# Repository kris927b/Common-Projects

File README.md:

# Common-Projects
Projects for AVR-C Microcontroller class KEA

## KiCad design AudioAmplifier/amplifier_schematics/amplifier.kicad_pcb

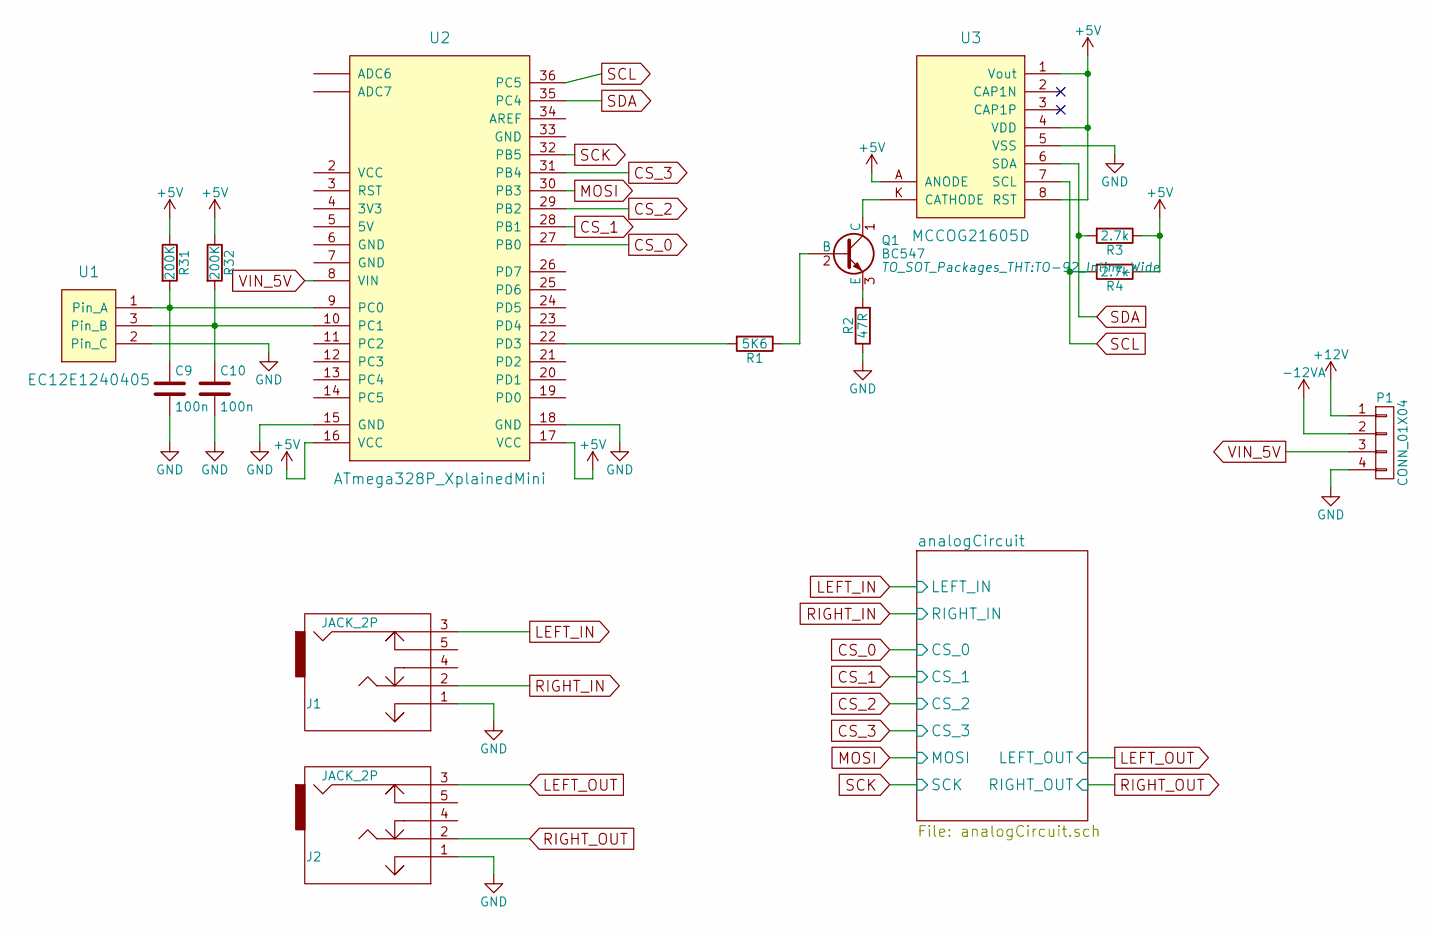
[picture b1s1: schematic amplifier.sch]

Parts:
C9, C10: 100n; C_Disc_D3.0mm_W1.6mm_P2.50mm
J1, J2: JACK_2P; JACK_3,5mm_5pin
P1: CONN_01X04; TerminalBlock_Pheonix_MKDS1.5-4pol
Q1: BC547; TO-92_Inline_Wide
R1: 5K6; R_Axial_DIN0207_L6.3mm_D2.5mm_P10.16mm_Horizontal
R2: 47R; R_Axial_DIN0207_L6.3mm_D2.5mm_P10.16mm_Horizontal
R3, R4: 2.7k; R_Axial_DIN0207_L6.3mm_D2.5mm_P10.16mm_Horizontal
R31, R32: 200K; R_Axial_DIN0207_L6.3mm_D2.5mm_P10.16mm_Horizontal
U1: EC12E1240405; Encoder EC12E
U2: ATmega328P_XplainedMini; xplained_board
U3: MCCOG21605D

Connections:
+5V: R3.1, R4.1, R31.1, R32.1, U2.16 (VCC), U2.17 (VCC), U3.1 (Vout), U3.4 (VDD), U3.8 (RST), U3.A (ANODE); also elsewhere on the board
+12V: P1.1; also elsewhere on the board
-12VA: P1.2; also elsewhere on the board
CS_0: U2.27 (PB0); also elsewhere on the board
CS_1: U2.28 (PB1); also elsewhere on the board
CS_2: U2.29 (PB2); also elsewhere on the board
CS_3: U2.31 (PB4); also elsewhere on the board
GND: C9.2, C10.2, J1.1, J2.1, P1.4, R2.1, U1.2 (Pin_C), U2.15 (GND), U2.18 (GND), U3.5 (VSS); also elsewhere on the board
LEFT_IN: J1.3; also elsewhere on the board
LEFT_OUT: J2.3; also elsewhere on the board
MOSI: U2.30 (PB3); also elsewhere on the board
unnamed: C9.1, R31.2, U1.1 (Pin_A), U2.9 (PC0)
unnamed: C10.1, R32.2, U1.3 (Pin_B), U2.10 (PC1)
unnamed: Q1.1 (C), U3.K (CATHODE)
unnamed: Q1.2 (B), R1.1
unnamed: Q1.3 (E), R2.2
unnamed: R1.2, U2.22 (PD3)
RIGHT_IN: J1.2; also elsewhere on the board
RIGHT_OUT: J2.2; also elsewhere on the board
SCK: U2.32 (PB5); also elsewhere on the board
SCL: R4.2, U2.36 (PC5), U3.7 (SCL)
SDA: R3.2, U2.35 (PC4), U3.6 (SDA)
VIN_5V: P1.3, U2.8 (VIN)

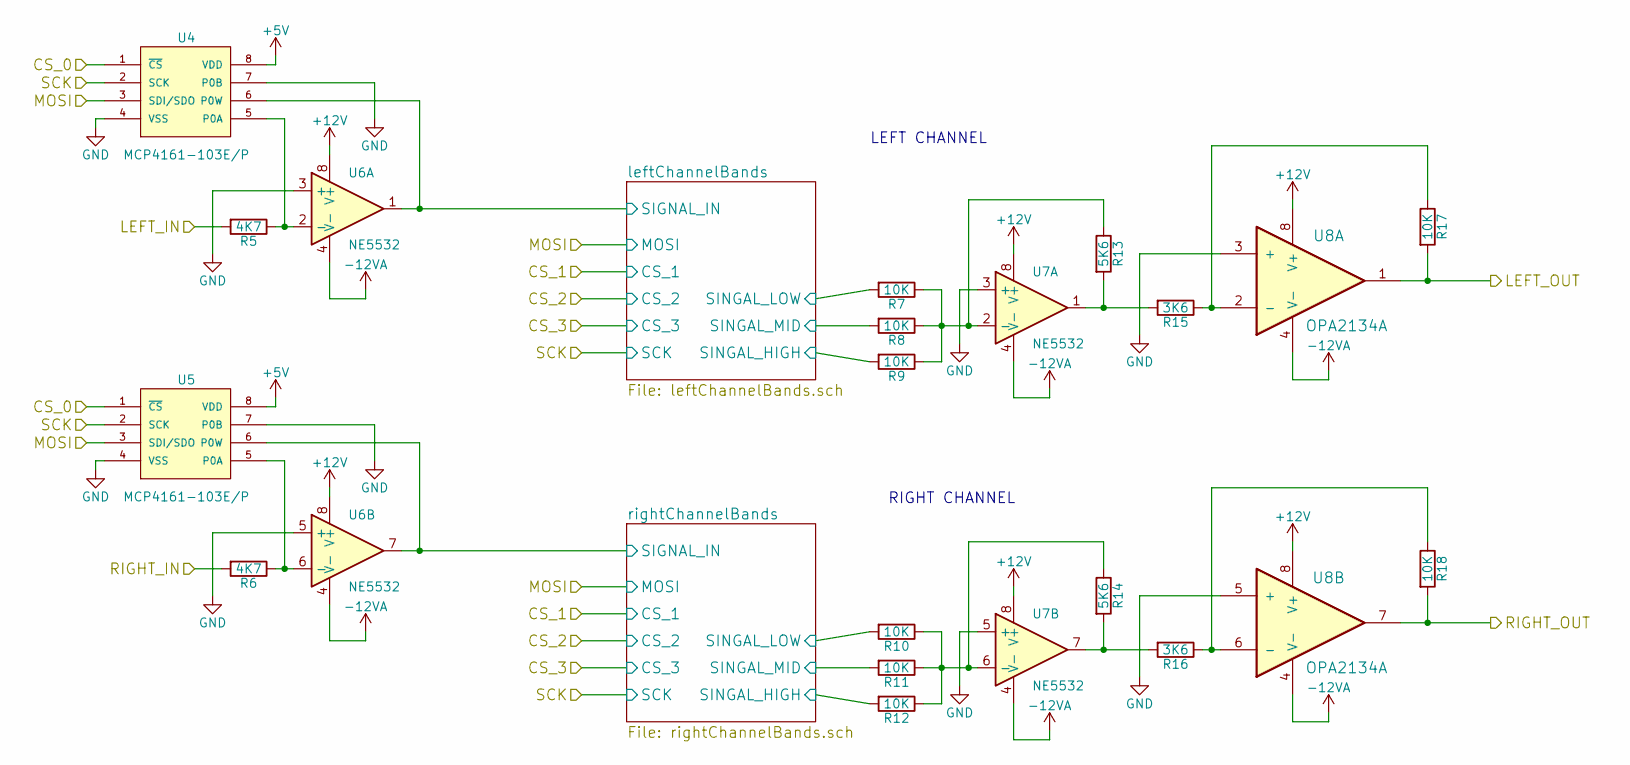
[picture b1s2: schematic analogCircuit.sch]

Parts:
R5, R6: 4K7; R_Axial_DIN0207_L6.3mm_D2.5mm_P10.16mm_Horizontal
R7, R8, R9, R10, R11, R12, R17, R18: 10K; R_Axial_DIN0207_L6.3mm_D2.5mm_P10.16mm_Horizontal
R13, R14: 5K6; R_Axial_DIN0207_L6.3mm_D2.5mm_P10.16mm_Horizontal
R15, R16: 3K6; R_Axial_DIN0207_L6.3mm_D2.5mm_P10.16mm_Horizontal
U4, U5: MCP4161-103E/P; DIP254P762X533-8
U6, U7: NE5532; DIP254P762X533-8
U8: OPA2134A; DIP254P762X533-8

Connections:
+5V: U4.8 (VDD), U5.8 (VDD); also elsewhere on the board
+12V: U6.8 (V+), U7.8 (V+), U8.8 (V+); also elsewhere on the board
-12VA: U6.4 (V-), U7.4 (V-), U8.4 (V-); also elsewhere on the board
/analogCircuit/leftChannelBands/SIGNAL_IN: U4.6 (P0W), U6.1; also elsewhere on the board
/analogCircuit/leftChannelBands/SINGAL_HIGH: R9.2; also elsewhere on the board
/analogCircuit/leftChannelBands/SINGAL_LOW: R7.2; also elsewhere on the board
/analogCircuit/leftChannelBands/SINGAL_MID: R8.2; also elsewhere on the board
/analogCircuit/rightChannelBands/SIGNAL_IN: U5.6 (P0W), U6.7; also elsewhere on the board
/analogCircuit/rightChannelBands/SINGAL_HIGH: R12.2; also elsewhere on the board
/analogCircuit/rightChannelBands/SINGAL_LOW: R10.2; also elsewhere on the board
/analogCircuit/rightChannelBands/SINGAL_MID: R11.2; also elsewhere on the board
CS_0: U4.1 (~CS), U5.1 (~CS); also elsewhere on the board
GND: U4.4 (VSS), U4.7 (P0B), U5.4 (VSS), U5.7 (P0B), U6.3 (+), U6.5 (+), U7.3 (+), U7.5 (+), U8.3 (+), U8.5 (+); also elsewhere on the board
LEFT_IN: R5.2; also elsewhere on the board
LEFT_OUT: R17.2, U8.1; also elsewhere on the board
MOSI: U4.3 (SDI/SDO), U5.3 (SDI/SDO); also elsewhere on the board
unnamed: R5.1, U4.5 (P0A), U6.2 (-)
unnamed: R6.1, U5.5 (P0A), U6.6 (-)
unnamed: R10.1, R11.1, R12.1, R14.1, U7.6 (-)
unnamed: R7.1, R8.1, R9.1, R13.1, U7.2 (-)
unnamed: R13.2, R15.2, U7.1
unnamed: R14.2, R16.2, U7.7
unnamed: R15.1, R17.1, U8.2 (-)
unnamed: R16.1, R18.1, U8.6 (-)
RIGHT_IN: R6.2; also elsewhere on the board
RIGHT_OUT: R18.2, U8.7; also elsewhere on the board
SCK: U4.2 (SCK), U5.2 (SCK); also elsewhere on the board

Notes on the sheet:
LEFT CHANNEL
RIGHT CHANNEL

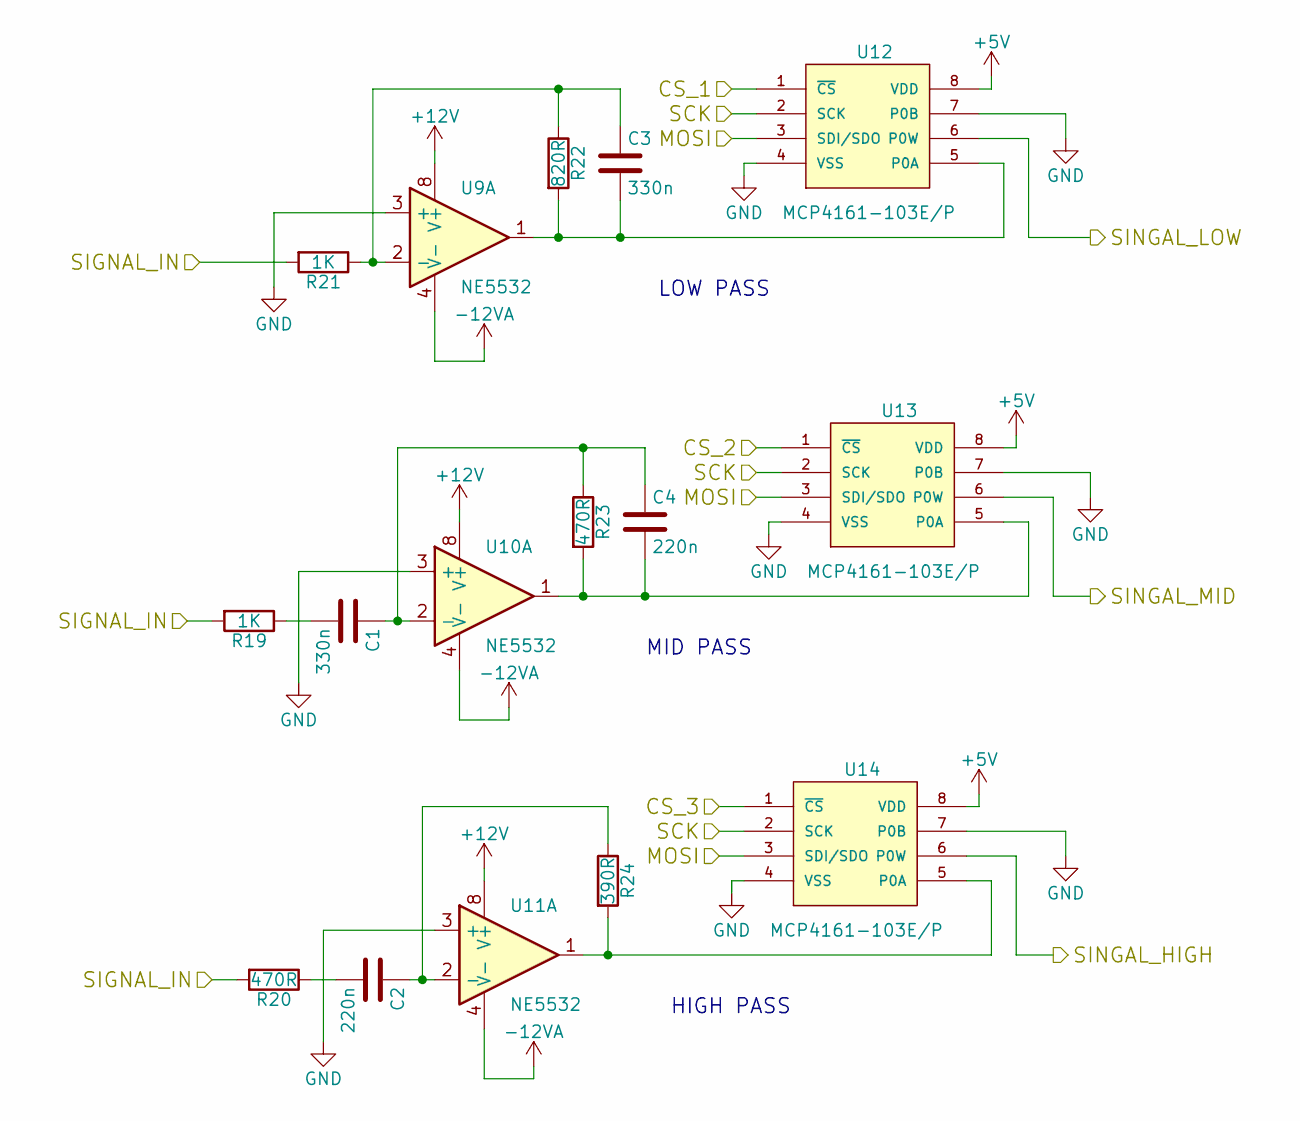
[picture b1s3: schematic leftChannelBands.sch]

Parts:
C1, C3: 330n; C_Rect_L7.0mm_W4.5mm_P5.00mm
C2, C4: 220n; C_Rect_L7.0mm_W4.5mm_P5.00mm
R19, R21: 1K; R_Axial_DIN0207_L6.3mm_D2.5mm_P10.16mm_Horizontal
R20, R23: 470R; R_Axial_DIN0207_L6.3mm_D2.5mm_P10.16mm_Horizontal
R22: 820R; R_Axial_DIN0207_L6.3mm_D2.5mm_P10.16mm_Horizontal
R24: 390R; R_Axial_DIN0207_L6.3mm_D2.5mm_P10.16mm_Horizontal
U9, U10, U11: NE5532; DIP254P762X533-8
U12, U13, U14: MCP4161-103E/P; DIP254P762X533-8

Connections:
+5V: U12.8 (VDD), U13.8 (VDD), U14.8 (VDD); also elsewhere on the board
+12V: U9.8 (V+), U10.8 (V+), U11.8 (V+); also elsewhere on the board
-12VA: U9.4 (V-), U10.4 (V-), U11.4 (V-); also elsewhere on the board
/analogCircuit/leftChannelBands/SIGNAL_IN: R19.2, R20.2, R21.2; also elsewhere on the board
/analogCircuit/leftChannelBands/SINGAL_HIGH: U14.6 (P0W); also elsewhere on the board
/analogCircuit/leftChannelBands/SINGAL_LOW: U12.6 (P0W); also elsewhere on the board
/analogCircuit/leftChannelBands/SINGAL_MID: U13.6 (P0W); also elsewhere on the board
CS_1: U12.1 (~CS); also elsewhere on the board
CS_2: U13.1 (~CS); also elsewhere on the board
CS_3: U14.1 (~CS); also elsewhere on the board
GND: U9.3 (+), U10.3 (+), U11.3 (+), U12.4 (VSS), U12.7 (P0B), U13.4 (VSS), U13.7 (P0B), U14.4 (VSS), U14.7 (P0B); also elsewhere on the board
MOSI: U12.3 (SDI/SDO), U13.3 (SDI/SDO), U14.3 (SDI/SDO); also elsewhere on the board
unnamed: C1.1, C4.1, R23.1, U10.2 (-)
unnamed: C1.2, R19.1
unnamed: C2.1, R24.1, U11.2 (-)
unnamed: C2.2, R20.1
unnamed: C3.1, R21.1, R22.1, U9.2 (-)
unnamed: C3.2, R22.2, U9.1, U12.5 (P0A)
unnamed: C4.2, R23.2, U10.1, U13.5 (P0A)
unnamed: R24.2, U11.1, U14.5 (P0A)
SCK: U12.2 (SCK), U13.2 (SCK), U14.2 (SCK); also elsewhere on the board

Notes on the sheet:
LOW PASS
MID PASS
HIGH PASS

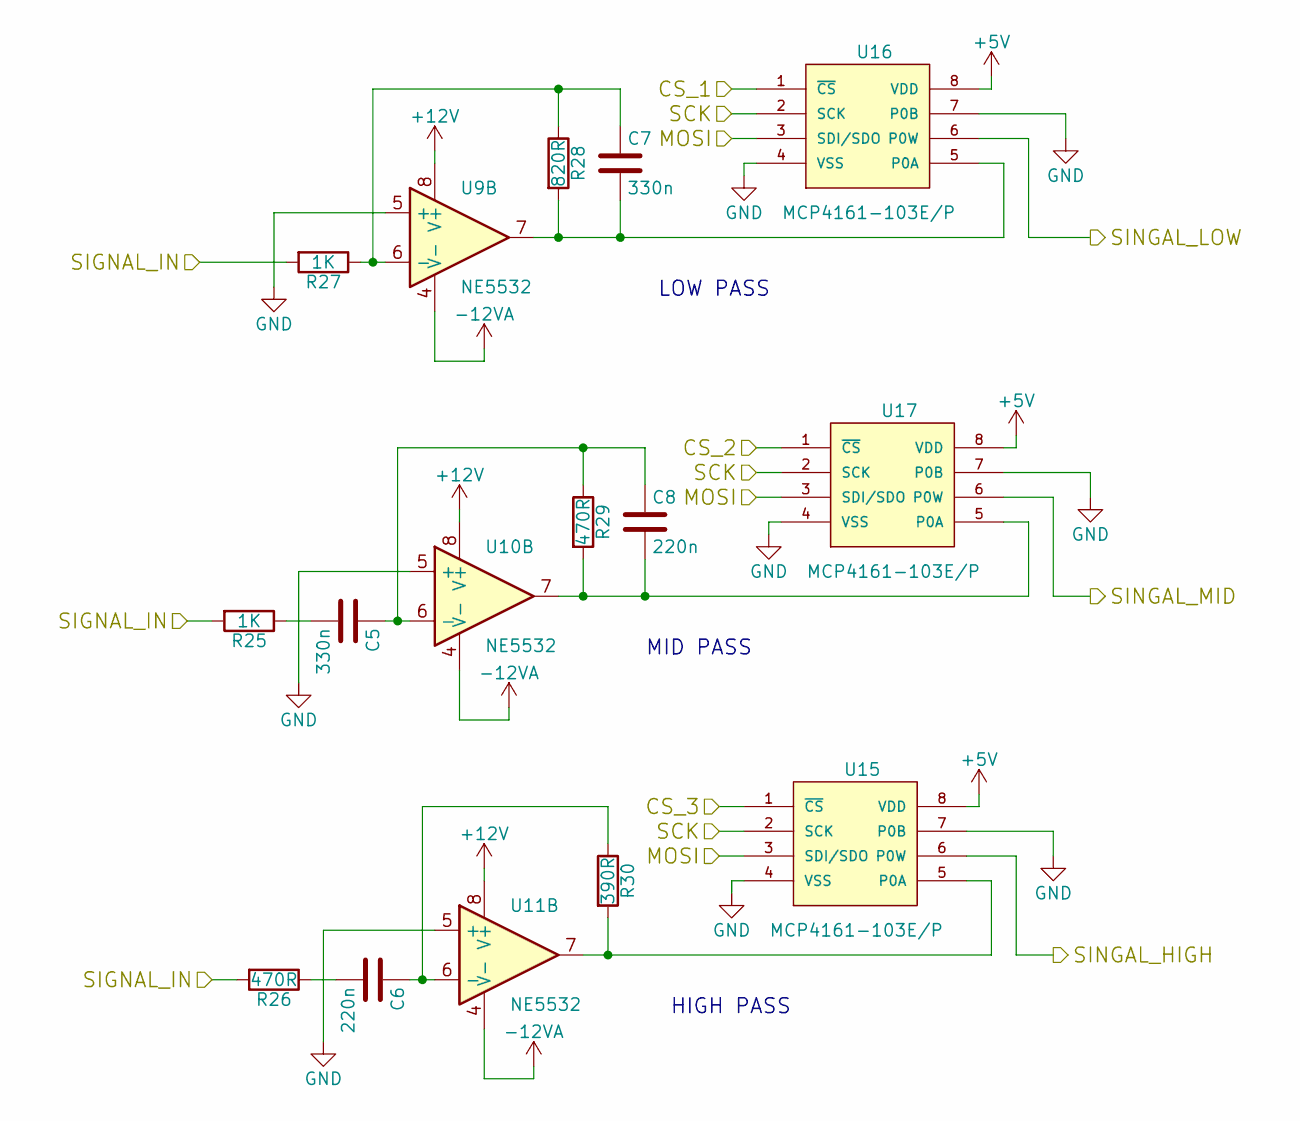
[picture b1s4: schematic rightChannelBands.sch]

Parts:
C5, C7: 330n; C_Rect_L7.0mm_W4.5mm_P5.00mm
C6, C8: 220n; C_Rect_L7.0mm_W4.5mm_P5.00mm
R25, R27: 1K; R_Axial_DIN0207_L6.3mm_D2.5mm_P10.16mm_Horizontal
R26, R29: 470R; R_Axial_DIN0207_L6.3mm_D2.5mm_P10.16mm_Horizontal
R28: 820R; R_Axial_DIN0207_L6.3mm_D2.5mm_P10.16mm_Horizontal
R30: 390R; R_Axial_DIN0207_L6.3mm_D2.5mm_P10.16mm_Horizontal
U9, U10, U11: NE5532; DIP254P762X533-8
U15, U16, U17: MCP4161-103E/P; DIP254P762X533-8

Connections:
+5V: U15.8 (VDD), U16.8 (VDD), U17.8 (VDD); also elsewhere on the board
+12V: U9.8 (V+), U10.8 (V+), U11.8 (V+); also elsewhere on the board
-12VA: U9.4 (V-), U10.4 (V-), U11.4 (V-); also elsewhere on the board
/analogCircuit/rightChannelBands/SIGNAL_IN: R25.2, R26.2, R27.2; also elsewhere on the board
/analogCircuit/rightChannelBands/SINGAL_HIGH: U15.6 (P0W); also elsewhere on the board
/analogCircuit/rightChannelBands/SINGAL_LOW: U16.6 (P0W); also elsewhere on the board
/analogCircuit/rightChannelBands/SINGAL_MID: U17.6 (P0W); also elsewhere on the board
CS_1: U16.1 (~CS); also elsewhere on the board
CS_2: U17.1 (~CS); also elsewhere on the board
CS_3: U15.1 (~CS); also elsewhere on the board
GND: U9.5 (+), U10.5 (+), U11.5 (+), U15.4 (VSS), U15.7 (P0B), U16.4 (VSS), U16.7 (P0B), U17.4 (VSS), U17.7 (P0B); also elsewhere on the board
MOSI: U15.3 (SDI/SDO), U16.3 (SDI/SDO), U17.3 (SDI/SDO); also elsewhere on the board
unnamed: C5.1, C8.1, R29.1, U10.6 (-)
unnamed: C5.2, R25.1
unnamed: C6.1, R30.1, U11.6 (-)
unnamed: C6.2, R26.1
unnamed: C7.1, R27.1, R28.1, U9.6 (-)
unnamed: C7.2, R28.2, U9.7, U16.5 (P0A)
unnamed: C8.2, R29.2, U10.7, U17.5 (P0A)
unnamed: R30.2, U11.7, U15.5 (P0A)
SCK: U15.2 (SCK), U16.2 (SCK), U17.2 (SCK); also elsewhere on the board

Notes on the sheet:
LOW PASS
MID PASS
HIGH PASS

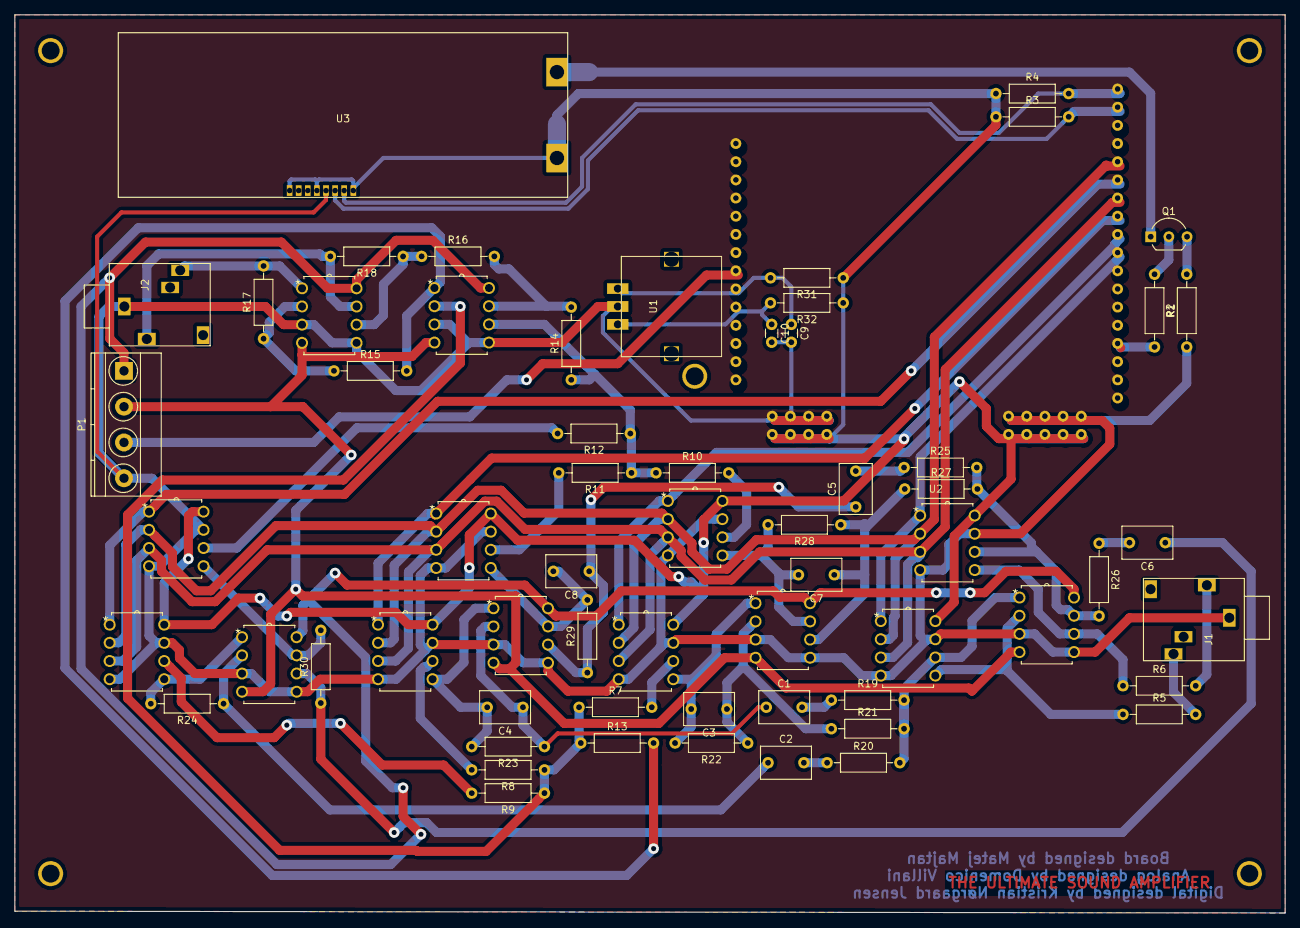
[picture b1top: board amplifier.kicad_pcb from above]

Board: 2 copper layers, 177.5 x 125.5 mm, 63 parts (0 on the bottom side), 55 nets.

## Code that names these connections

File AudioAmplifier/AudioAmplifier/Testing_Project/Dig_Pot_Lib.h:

/*
 * Dig_Pot_Lib.h
 *
 * Created: 4/21/2017 9:35:26 AM
 *  Author: Kristian Nørgaard Jensen
 */ 


#ifndef DIG_POT_LIB_H_
#define DIG_POT_LIB_H_

#define CS_0 PINB0 // Master Pot meter
#define CS_1 PINB1 // Bass Pot meter
#define CS_2 PINB2 // Mid-Range Pot meter
#define CS_3 PINB4 // Treble Pot meter
#define CS_D DDRB
#define CS PORTB

#include <avr/io.h>

void Init_Pot_Meter(void);
void Write_Pot_Meter(uint8_t value, uint8_t CS_pin);

#endif /* DIG_POT_LIB_H_ */

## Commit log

2017-03-30 Rotary safe added
2017-03-30 Different libraries added
2017-04-05 console menu vc++ edition added
    added first version on console menu in vc++ (Visual Studio)
2017-04-10 added AVR menu solution
    finished colored menu
2017-04-16 improved AVRmenu
2017-04-19 New folder
2017-04-19 Added Kicad File
    -with library
2017-04-19 Beginning of SPI library
2017-04-21 updated kicad file and avr menu
2017-04-21 Pot meter lib & SPI Lib
    Extended Spi lib, plus made a seperate Pot meter lib
2017-04-21 changed kicad files
2017-04-21 Created project for the digital part
2017-04-21 LTspice simulation for 1 channel
2017-04-21 kicad update
2017-04-21 added i2c lib
2017-04-21 Project logic in the process
2017-04-21 Logic in the main.c
2017-04-22 Removed hello.txt
2017-04-24 Project file
2017-04-24 updated i2c lib
    this time with code :/
2017-04-24 Main file
2017-04-24 Updated digital part
    LCD library added
    Send screen data function
    Started on the update display function
2017-04-24 Test project for SPI
2017-04-24 updated kicad file
2017-04-25 SPI return data
2017-04-26 SPI finally works
2017-04-27 Test
2017-04-27 kicad schem
2017-04-27 lt spice all inv
2017-05-01 i2c display project
    kinda working
2017-05-01 I2C Test
2017-05-01 Save
2017-05-03 LCD Work
2017-05-03 Menu is now ready
2017-05-03 Last Lt circuit project
2017-05-08 Building material
2017-05-08 Screen saver added, plus brightness control
2017-05-10 Comments to the menu
2017-05-10 Testing SPI on multiple pot meters + Creating function to update the system
2017-05-10 Testing full system
2017-05-15 Audio
2017-05-22 Tests
2017-05-22 kicad
2017-05-29 Amplifier project LtSpice
2017-05-29 Comments and library changes
2017-05-29 updated KICAD
